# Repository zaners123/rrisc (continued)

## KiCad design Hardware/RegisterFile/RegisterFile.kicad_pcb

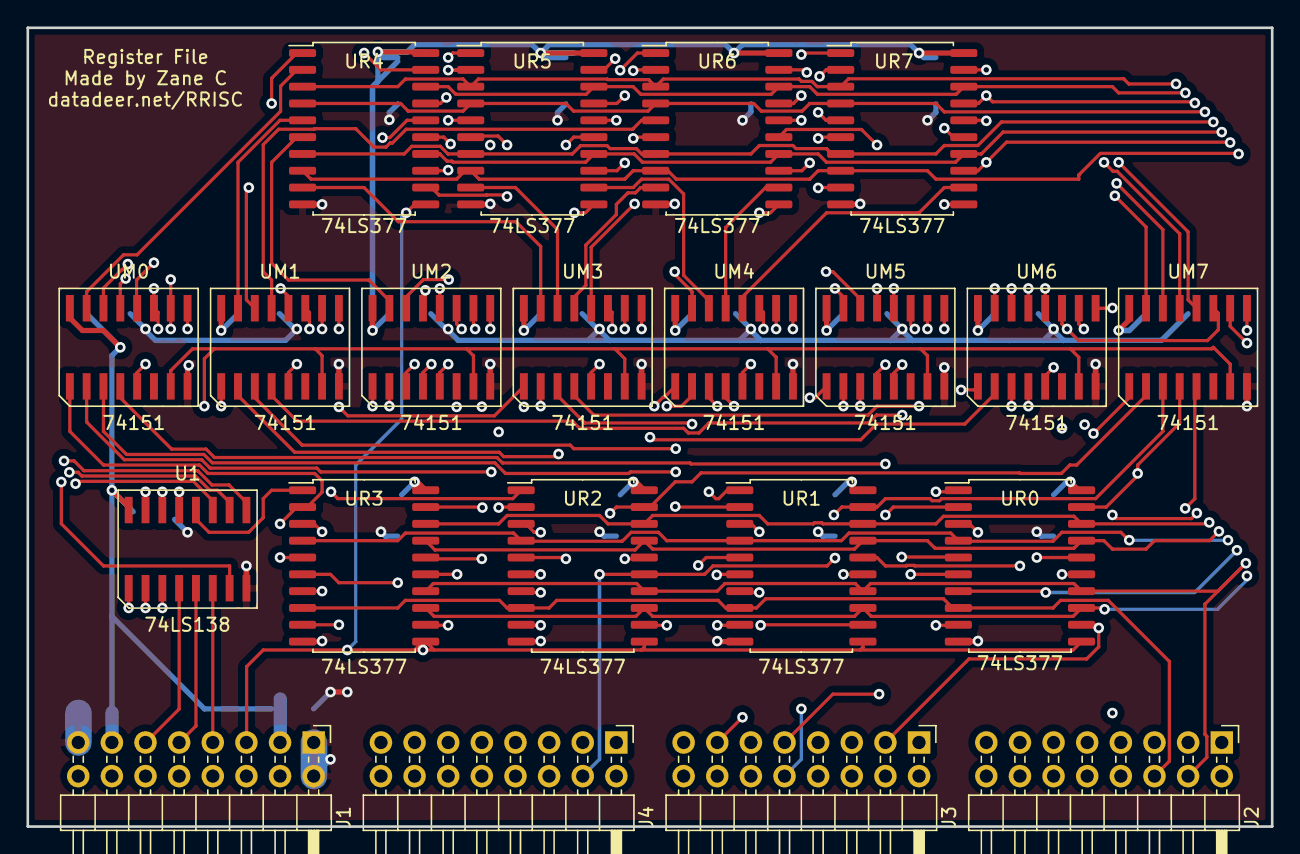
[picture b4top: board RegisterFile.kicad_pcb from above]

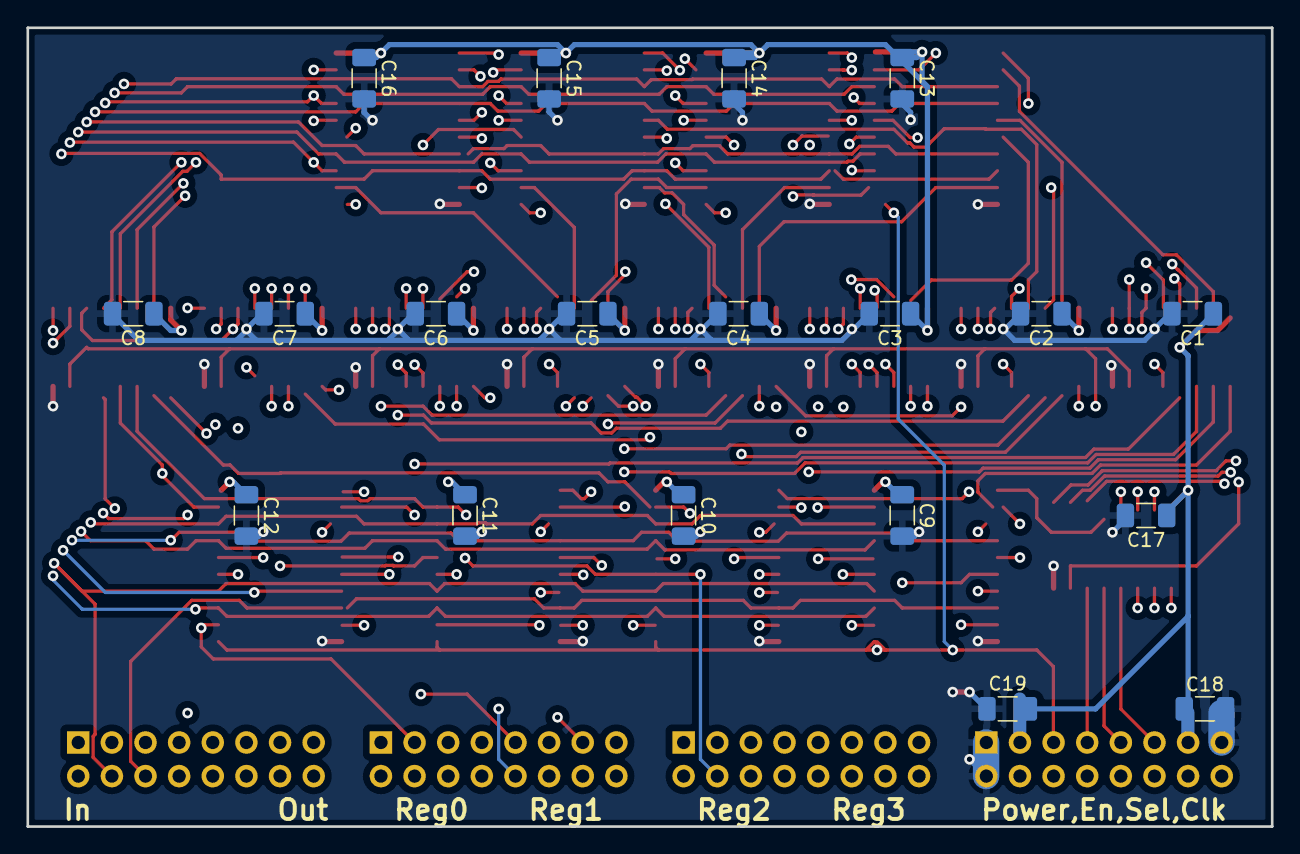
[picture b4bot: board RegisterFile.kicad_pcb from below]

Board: 4 copper layers, 94.0 x 60.3 mm, 40 parts (19 on the bottom side), 101 nets.

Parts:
C1, C2, C3, C4, C5, C6, C7, C8, C9, C10, C11, C12, C13, C14, C15, C16, C17, C18, C19: .1uF; C_1206_3216Metric_Pad1.33x1.80mm_HandSolder
J1, J2, J3, J4: Conn_02x08_Odd_Even; PinHeader_2x08_P2.54mm_Horizontal
U1: 74LS138; R-PDSO-G16
UM0, UM1, UM2, UM3, UM4, UM5, UM6, UM7: 74151; R-PDSO-G16
UR0, UR1, UR2, UR3, UR4, UR5, UR6, UR7: 74LS377; SOIC-20W_7.5x12.8mm_P1.27mm

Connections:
/CLK: J1.5, UR0.11 (CP), UR1.11 (CP), UR2.11 (CP), UR3.11 (CP), UR4.11 (CP), UR5.11 (CP), UR6.11 (CP), UR7.11 (CP)
/DATAIN0: J2.7, UR0.3 (D0), UR1.3 (D0), UR2.3 (D0), UR3.3 (D0), UR4.3 (D0), UR5.3 (D0), UR6.3 (D0), UR7.3 (D0)
/DATAIN1: J2.8, UR0.4 (D1), UR1.4 (D1), UR2.4 (D1), UR3.4 (D1), UR4.4 (D1), UR5.4 (D1), UR6.4 (D1), UR7.4 (D1)
/DATAIN2: J2.5, UR0.7 (D2), UR1.7 (D2), UR2.7 (D2), UR3.7 (D2), UR4.7 (D2), UR5.7 (D2), UR6.7 (D2), UR7.7 (D2)
/DATAIN3: J2.6, UR0.8 (D3), UR1.8 (D3), UR2.8 (D3), UR3.8 (D3), UR4.8 (D3), UR5.8 (D3), UR6.8 (D3), UR7.8 (D3)
/DATAIN4: J2.3, UR0.13 (D4), UR1.13 (D4), UR2.13 (D4), UR3.13 (D4), UR4.13 (D4), UR5.13 (D4), UR6.13 (D4), UR7.13 (D4)
/DATAIN5: J2.4, UR0.14 (D5), UR1.14 (D5), UR2.14 (D5), UR3.14 (D5), UR4.14 (D5), UR5.14 (D5), UR6.14 (D5), UR7.14 (D5)
/DATAIN6: J2.1, UR0.17 (D6), UR1.17 (D6), UR2.17 (D6), UR3.17 (D6), UR4.17 (D6), UR5.17 (D6), UR6.17 (D6), UR7.17 (D6)
/DATAIN7: J2.2, UR0.18 (D7), UR1.18 (D7), UR2.18 (D7), UR3.18 (D7), UR4.18 (D7), UR5.18 (D7), UR6.18 (D7), UR7.18 (D7)
/DATAOUT0: J2.15, UM0.5 (Q)
/DATAOUT1: J2.16, UM1.5 (Q)
/DATAOUT2: J2.13, UM2.5 (Q)
/DATAOUT3: J2.14, UM3.5 (Q)
/DATAOUT4: J2.11, UM4.5 (Q)
/DATAOUT5: J2.12, UM5.5 (Q)
/DATAOUT6: J2.9, UM6.5 (Q)
/DATAOUT7: J2.10, UM7.5 (Q)
/READID0: J1.16, UM0.11 (S0), UM1.11 (S0), UM2.11 (S0), UM3.11 (S0), UM4.11 (S0), UM5.11 (S0), UM6.11 (S0), UM7.11 (S0)
/READID1: J1.14, UM0.10 (S1), UM1.10 (S1), UM2.10 (S1), UM3.10 (S1), UM4.10 (S1), UM5.10 (S1), UM6.10 (S1), UM7.10 (S1)
/READID2: J1.12, UM0.9 (S2), UM1.9 (S2), UM2.9 (S2), UM3.9 (S2), UM4.9 (S2), UM5.9 (S2), UM6.9 (S2), UM7.9 (S2)
/REG0_0: J3.7, UM0.4 (I0), UR0.2 (Q0)
/REG0_1: J3.8, UM1.4 (I0), UR0.5 (Q1)
/REG0_2: J3.5, UM2.4 (I0), UR0.6 (Q2)
/REG0_3: J3.6, UM3.4 (I0), UR0.9 (Q3)
/REG0_4: J3.3, UM4.4 (I0), UR0.12 (Q4)
/REG0_5: J3.4, UM5.4 (I0), UR0.15 (Q5)
/REG0_6: J3.1, UM6.4 (I0), UR0.16 (Q6)
/REG0_7: J3.2, UM7.4 (I0), UR0.19 (Q7)
/REG1_0: J3.15, UM0.3 (I1), UR1.2 (Q0)
/REG1_1: J3.16, UM1.3 (I1), UR1.5 (Q1)
/REG1_2: J3.13, UM2.3 (I1), UR1.6 (Q2)
/REG1_3: J3.14, UM3.3 (I1), UR1.9 (Q3)
/REG1_4: J3.11, UM4.3 (I1), UR1.12 (Q4)
/REG1_5: J3.12, UM5.3 (I1), UR1.15 (Q5)
/REG1_6: J3.9, UM6.3 (I1), UR1.16 (Q6)
/REG1_7: J3.10, UM7.3 (I1), UR1.19 (Q7)
/REG2_0: J4.7, UM0.2 (I2), UR2.2 (Q0)
/REG2_1: J4.8, UM1.2 (I2), UR2.5 (Q1)
/REG2_2: J4.5, UM2.2 (I2), UR2.6 (Q2)
/REG2_3: J4.6, UM3.2 (I2), UR2.9 (Q3)
/REG2_4: J4.3, UM4.2 (I2), UR2.12 (Q4)
/REG2_5: J4.4, UM5.2 (I2), UR2.15 (Q5)
/REG2_6: J4.1, UM6.2 (I2), UR2.16 (Q6)
/REG2_7: J4.2, UM7.2 (I2), UR2.19 (Q7)
/REG3_0: J4.15, UM0.1 (I3), UR3.2 (Q0)
/REG3_1: J4.16, UM1.1 (I3), UR3.5 (Q1)
/REG3_2: J4.13, UM2.1 (I3), UR3.6 (Q2)
/REG3_3: J4.14, UM3.1 (I3), UR3.9 (Q3)
/REG3_4: J4.11, UM4.1 (I3), UR3.12 (Q4)
/REG3_5: J4.12, UM5.1 (I3), UR3.15 (Q5)
/REG3_6: J4.9, UM6.1 (I3), UR3.16 (Q6)
/REG3_7: J4.10, UM7.1 (I3), UR3.19 (Q7)
/REG4_0: UM0.15 (I4), UR4.2 (Q0)
/REG4_1: UM1.15 (I4), UR4.5 (Q1)
/REG4_2: UM2.15 (I4), UR4.6 (Q2)
/REG4_3: UM3.15 (I4), UR4.9 (Q3)
/REG4_4: UM4.15 (I4), UR4.12 (Q4)
/REG4_5: UM5.15 (I4), UR4.15 (Q5)
/REG4_6: UM6.15 (I4), UR4.16 (Q6)
/REG4_7: UM7.15 (I4), UR4.19 (Q7)
/REG5_0: UM0.14 (I5), UR5.2 (Q0)
/REG5_1: UM1.14 (I5), UR5.5 (Q1)
/REG5_2: UM2.14 (I5), UR5.6 (Q2)
/REG5_3: UM3.14 (I5), UR5.9 (Q3)
/REG5_4: UM4.14 (I5), UR5.12 (Q4)
/REG5_5: UM5.14 (I5), UR5.15 (Q5)
/REG5_6: UM6.14 (I5), UR5.16 (Q6)
/REG5_7: UM7.14 (I5), UR5.19 (Q7)
/REG6_0: UM0.13 (I6), UR6.2 (Q0)
/REG6_1: UM1.13 (I6), UR6.5 (Q1)
/REG6_2: UM2.13 (I6), UR6.6 (Q2)
/REG6_3: UM3.13 (I6), UR6.9 (Q3)
/REG6_4: UM4.13 (I6), UR6.12 (Q4)
/REG6_5: UM5.13 (I6), UR6.15 (Q5)
/REG6_6: UM6.13 (I6), UR6.16 (Q6)
/REG6_7: UM7.13 (I6), UR6.19 (Q7)
/REG7_0: UM0.12 (I7), UR7.2 (Q0)
/REG7_1: UM1.12 (I7), UR7.5 (Q1)
/REG7_2: UM2.12 (I7), UR7.6 (Q2)
/REG7_3: UM3.12 (I7), UR7.9 (Q3)
/REG7_4: UM4.12 (I7), UR7.12 (Q4)
/REG7_5: UM5.12 (I7), UR7.15 (Q5)
/REG7_6: UM6.12 (I7), UR7.16 (Q6)
/REG7_7: UM7.12 (I7), UR7.19 (Q7)
/Regs/~WRITESEL0: U1.15 (~Y0), UR0.1 (~E)
/Regs/~WRITESEL1: U1.14 (~Y1), UR1.1 (~E)
/Regs/~WRITESEL2: U1.13 (~Y2), UR2.1 (~E)
/Regs/~WRITESEL3: U1.12 (~Y3), UR3.1 (~E)
/Regs/~WRITESEL4: U1.11 (~Y4), UR4.1 (~E)
/Regs/~WRITESEL5: U1.10 (~Y5), UR5.1 (~E)
/Regs/~WRITESEL6: U1.9 (~Y6), UR6.1 (~E)
/Regs/~WRITESEL7: U1.7 (~Y7), UR7.1 (~E)
/WEN2: J1.7, U1.6 (G1)
/WRITEID0: J1.10, U1.1 (A0)
/WRITEID1: J1.8, U1.2 (A1)
/WRITEID2: J1.6, U1.3 (A2)
/~REN: J1.4, UM0.7 (~E), UM1.7 (~E), UM2.7 (~E), UM3.7 (~E), UM4.7 (~E), UM5.7 (~E), UM6.7 (~E), UM7.7 (~E)
/~WEN0: J1.11, U1.4 (~G2A)
/~WEN1: J1.9, U1.5 (~G2B)
GND: C1.2, C2.2, C3.2, C4.2, C5.2, C6.2, C7.2, C8.2, C9.2, C10.2, C11.2, C12.2, C13.2, C14.2, C15.2, C16.2, C17.2, C18.2, C19.2, J1.1, J1.2, J1.15, U1.8 (GND), UM0.8 (GND), UM1.8 (GND), UM2.8 (GND), UM3.8 (GND), UM4.8 (GND), UM5.8 (GND), UM6.8 (GND), UM7.8 (GND), UR0.10 (GND), UR1.10 (GND), UR2.10 (GND), UR3.10 (GND), UR4.10 (GND), UR5.10 (GND), UR6.10 (GND), UR7.10 (GND)
VCC: C1.1, C2.1, C3.1, C4.1, C5.1, C6.1, C7.1, C8.1, C9.1, C10.1, C11.1, C12.1, C13.1, C14.1, C15.1, C16.1, C17.1, C18.1, C19.1, J1.3, J1.13, U1.16 (VCC), UM0.16 (VCC), UM1.16 (VCC), UM2.16 (VCC), UM3.16 (VCC), UM4.16 (VCC), UM5.16 (VCC), UM6.16 (VCC), UM7.16 (VCC), UR0.20 (VCC), UR1.20 (VCC), UR2.20 (VCC), UR3.20 (VCC), UR4.20 (VCC), UR5.20 (VCC), UR6.20 (VCC), UR7.20 (VCC)

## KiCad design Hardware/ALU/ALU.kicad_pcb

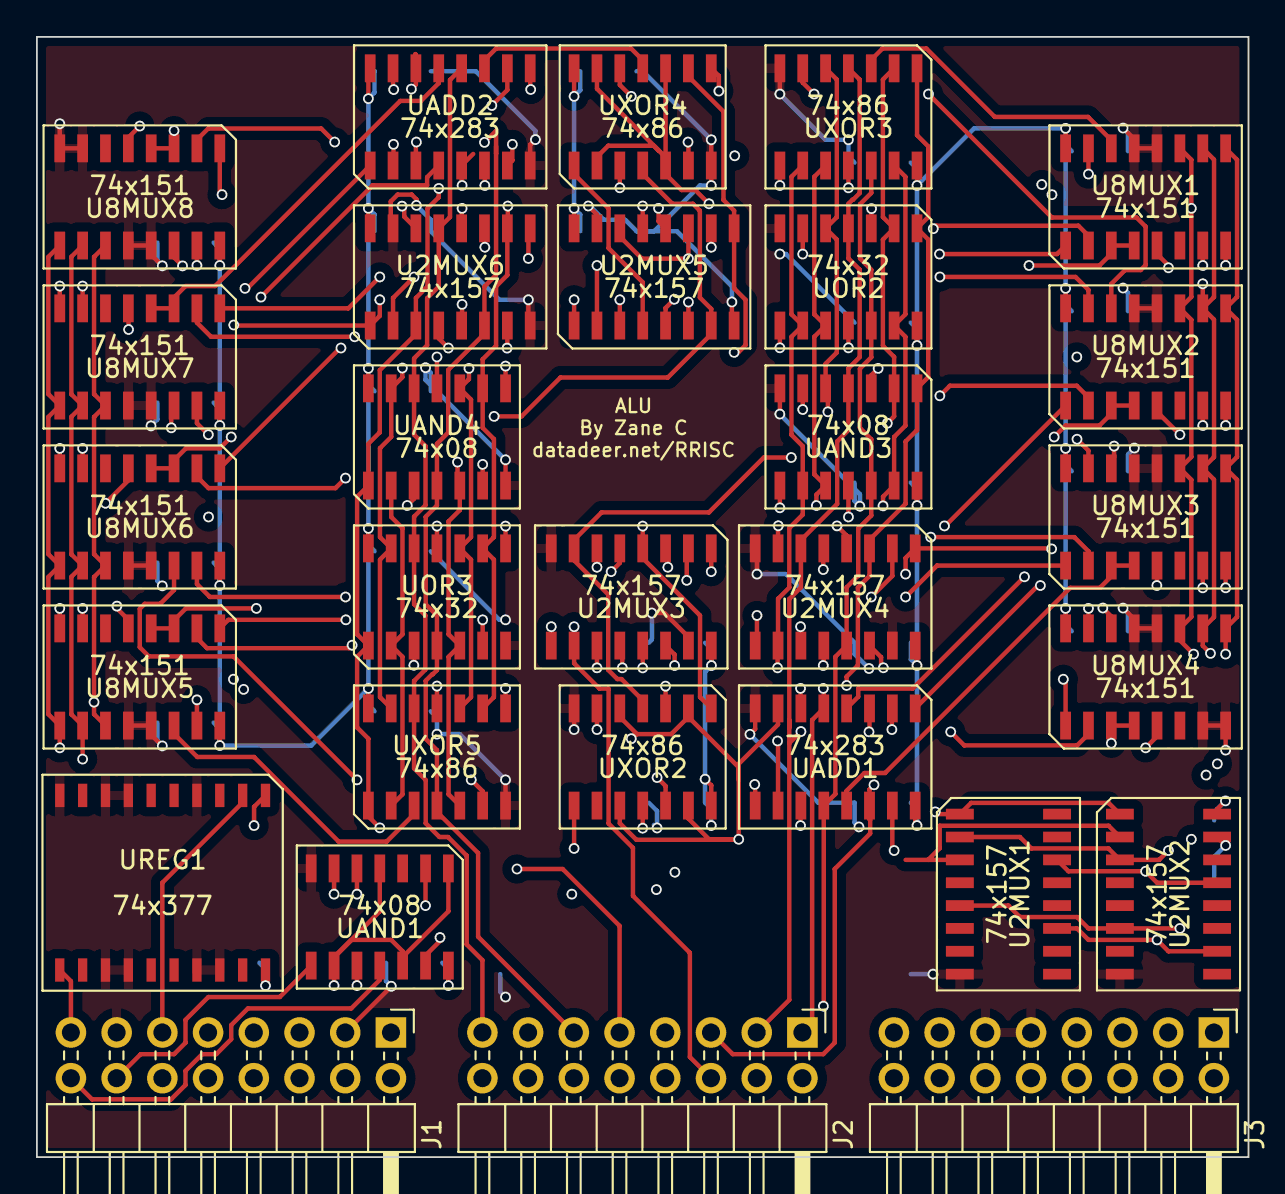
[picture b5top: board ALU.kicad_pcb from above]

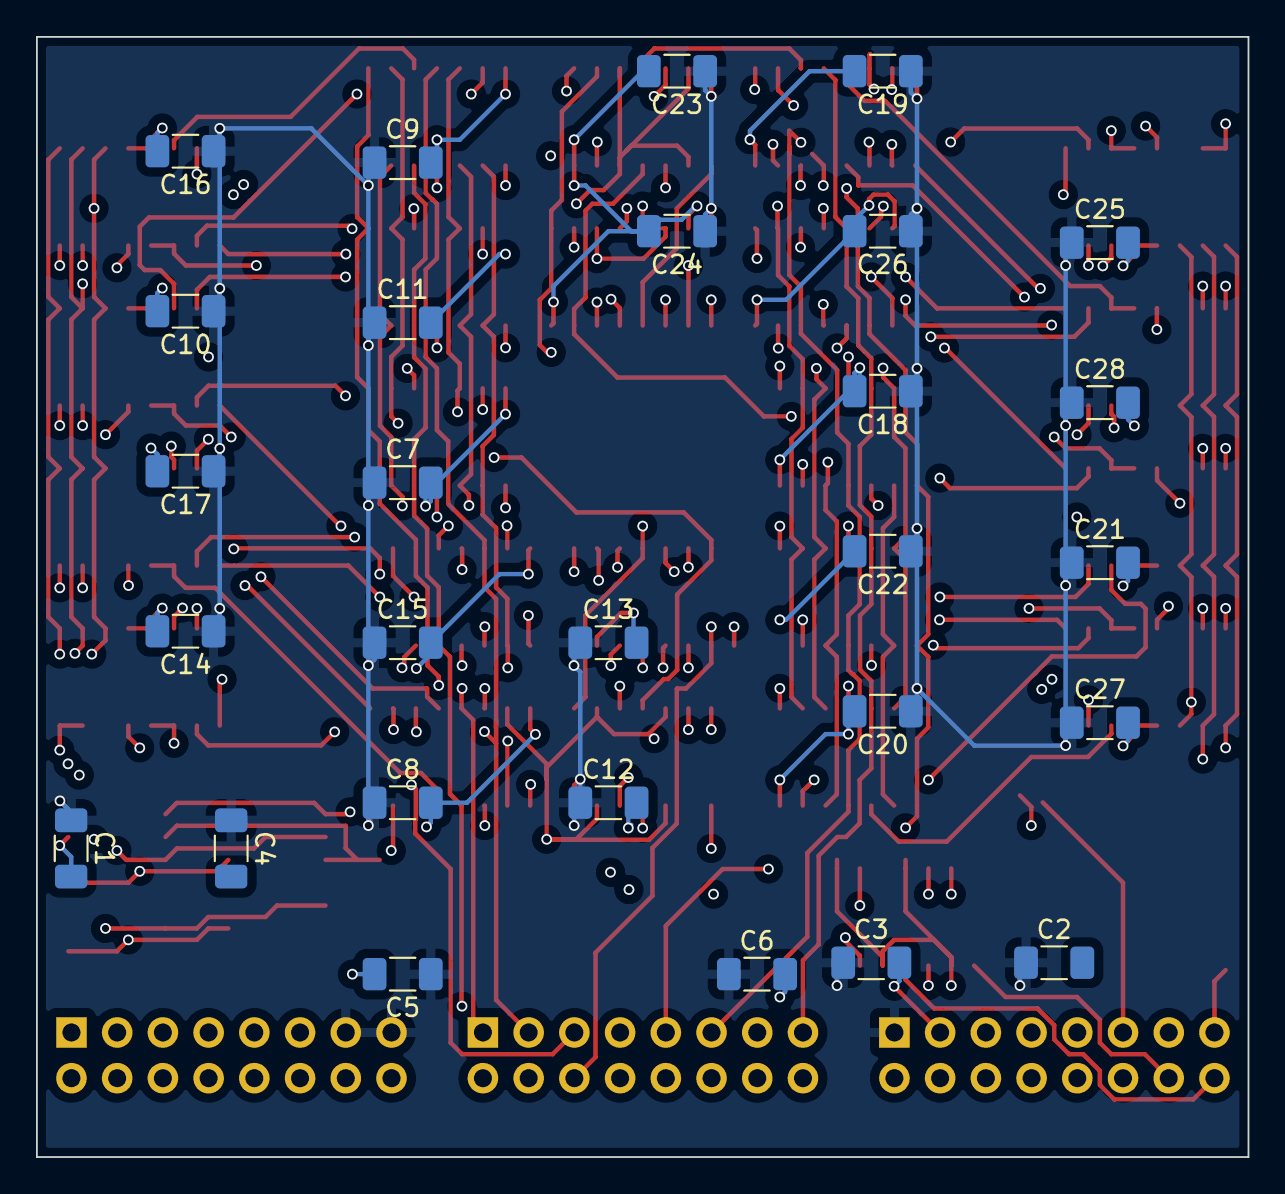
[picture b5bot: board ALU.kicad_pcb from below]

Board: 4 copper layers, 67.3 x 62.2 mm, 57 parts (28 on the bottom side), 109 nets.

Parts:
C1, C2, C3, C4, C5, C6, C7, C8, C9, C10, C11, C12, C13, C14, C15, C16, C17, C18, C19, C20, C21, C22, C23, C24, C25, C26, C27, C28: .1uF; C_1206_3216Metric_Pad1.33x1.80mm_HandSolder
J1, J2, J3: connector_2x8; PinHeader_2x08_P2.54mm_Horizontal
U2MUX1, U2MUX2, U2MUX3, U2MUX4, U2MUX5, U2MUX6: 74x157; D_R-PDSO-G16
U8MUX1, U8MUX2, U8MUX3, U8MUX4, U8MUX5, U8MUX6, U8MUX7, U8MUX8: 74x151; D_R-PDSO-G16
UADD1, UADD2: 74x283; D_R-PDSO-G16
UAND1, UAND3, UAND4: 74x08; D_R-PDSO-G14
UOR2, UOR3: 74x32; D_R-PDSO-G14
UREG1: 74x377; ON-SOIC20-WB
UXOR2, UXOR3, UXOR4, UXOR5: 74x86; D_R-PDSO-G14

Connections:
/CARRY_BETWEEN: UADD1.9 (C4), UADD2.7 (C0)
/CHANGEOUT: J1.5, UAND1.1, UAND1.4, UAND1.9, UAND1.12
/CLK: J1.15, UREG1.11 (CP)
/IN_ACC0: J2.1, U2MUX4.3 (I1a), UADD1.5 (A1), UAND3.1, UOR2.1, UXOR3.1
/IN_ACC1: J2.3, U2MUX4.6 (I1b), UADD1.3 (A2), UAND3.4, UOR2.4, UXOR3.4
/IN_ACC2: J2.5, U2MUX4.10 (I1c), UADD1.14 (A3), UAND3.9, UOR2.9, UXOR3.9
/IN_ACC3: J2.7, U2MUX4.13 (I1d), UADD1.12 (A4), UAND3.12, UOR2.12, UXOR3.12
/IN_ACC4: J2.9, U2MUX6.3 (I1a), UADD2.5 (A1), UAND4.1, UOR3.1, UXOR5.1
/IN_ACC5: J2.11, U2MUX6.6 (I1b), UADD2.3 (A2), UAND4.4, UOR3.4, UXOR5.4
/IN_ACC6: J2.13, U2MUX6.10 (I1c), UADD2.14 (A3), UAND4.9, UOR3.9, UXOR5.9
/IN_ACC7: J2.15, U2MUX6.13 (I1d), UADD2.12 (A4), UAND4.12, UOR3.12, UXOR5.12
/IN_IMMEDIATE0: J1.2, U2MUX3.2 (I0a), UAND1.2
/IN_IMMEDIATE1: J1.4, U2MUX3.5 (I0b), UAND1.5
/IN_IMMEDIATE2: J1.6, U2MUX3.11 (I0c), UAND1.10
/IN_IMMEDIATE3: J1.8, U2MUX3.14 (I0d), UAND1.13
/IN_OPCODE0: J3.7, U2MUX3.1 (S), U2MUX4.1 (S), U2MUX5.1 (S), U2MUX6.1 (S)
/IN_OPCODE1: J3.5, U8MUX1.11 (S0), U8MUX2.11 (S0), U8MUX3.11 (S0), U8MUX4.11 (S0), U8MUX5.11 (S0), U8MUX6.11 (S0), U8MUX7.11 (S0), U8MUX8.11 (S0), UADD1.7 (C0), UXOR2.2, UXOR2.5, UXOR2.10, UXOR2.13, UXOR4.2, UXOR4.5, UXOR4.10, UXOR4.13
/IN_OPCODE2: J3.3, U2MUX5.2 (I0a), U2MUX5.5 (I0b), U2MUX5.11 (I0c), U2MUX5.14 (I0d), U8MUX1.10 (S1), U8MUX2.10 (S1), U8MUX3.10 (S1), U8MUX4.10 (S1), U8MUX5.10 (S1), U8MUX6.10 (S1), U8MUX7.10 (S1), U8MUX8.10 (S1)
/IN_OPCODE3: J3.1, U8MUX1.9 (S2), U8MUX2.9 (S2), U8MUX3.9 (S2), U8MUX4.9 (S2), U8MUX5.9 (S2), U8MUX6.9 (S2), U8MUX7.9 (S2), U8MUX8.9 (S2)
/IN_REGDATA0: J2.2, U2MUX3.3 (I1a), U2MUX4.2 (I0a)
/IN_REGDATA1: J2.4, U2MUX3.6 (I1b), U2MUX4.5 (I0b)
/IN_REGDATA2: J2.6, U2MUX3.10 (I1c), U2MUX4.11 (I0c)
/IN_REGDATA3: J2.8, U2MUX3.13 (I1d), U2MUX4.14 (I0d)
/IN_REGDATA4: J2.10, U2MUX5.3 (I1a), U2MUX6.2 (I0a)
/IN_REGDATA5: J2.12, U2MUX5.6 (I1b), U2MUX6.5 (I0b)
/IN_REGDATA6: J2.14, U2MUX5.10 (I1c), U2MUX6.11 (I0c)
/IN_REGDATA7: J2.16, U2MUX5.13 (I1d), U2MUX6.14 (I0d)
/OUT_CARRY: J1.11, UREG1.2 (Q0)
/OUT_RESULT0: J3.16, U2MUX1.4 (Za)
/OUT_RESULT1: J3.14, U2MUX1.7 (Zb)
/OUT_RESULT2: J3.12, U2MUX1.9 (Zc)
/OUT_RESULT3: J3.10, U2MUX1.12 (Zd)
/OUT_RESULT4: J3.8, U2MUX2.4 (Za)
/OUT_RESULT5: J3.6, U2MUX2.7 (Zb)
/OUT_RESULT6: J3.4, U2MUX2.9 (Zc)
/OUT_RESULT7: J3.2, U2MUX2.12 (Zd)
/OUT_RX_ID0: J1.10, UAND1.3
/OUT_RX_ID1: J1.12, UAND1.6
/OUT_RX_ID2: J1.14, UAND1.8
/OUT_RX_ID3: J1.16, UAND1.11
/PRESWAPPED0: U2MUX1.2 (I0a), U2MUX2.3 (I1a), U8MUX1.5 (Q)
/PRESWAPPED1: U2MUX1.5 (I0b), U2MUX2.6 (I1b), U8MUX2.5 (Q)
/PRESWAPPED2: U2MUX1.11 (I0c), U2MUX2.10 (I1c), U8MUX3.5 (Q)
/PRESWAPPED3: U2MUX1.14 (I0d), U2MUX2.13 (I1d), U8MUX4.5 (Q)
/PRESWAPPED4: U2MUX1.3 (I1a), U2MUX2.2 (I0a), U8MUX5.5 (Q)
/PRESWAPPED5: U2MUX1.6 (I1b), U2MUX2.5 (I0b), U8MUX6.5 (Q)
/PRESWAPPED6: U2MUX1.10 (I1c), U2MUX2.11 (I0c), U8MUX7.5 (Q)
/PRESWAPPED7: U2MUX1.13 (I1d), U2MUX2.14 (I0d), U8MUX8.5 (Q)
/SWAP_NIBBLES: J1.9, U2MUX1.1 (S), U2MUX2.1 (S)
/lower/OP0_BIT0: U8MUX1.3 (I1), U8MUX1.4 (I0), UADD1.4 (S1)
/lower/OP0_BIT1: U8MUX2.3 (I1), U8MUX2.4 (I0), UADD1.1 (S2)
/lower/OP0_BIT2: U8MUX3.3 (I1), U8MUX3.4 (I0), UADD1.13 (S3)
/lower/OP0_BIT3: U8MUX4.3 (I1), U8MUX4.4 (I0), UADD1.10 (S4)
/lower/OP2_BIT0: U8MUX1.2 (I2), UAND3.3
/lower/OP2_BIT1: U8MUX2.2 (I2), UAND3.6
/lower/OP2_BIT2: U8MUX3.2 (I2), UAND3.8
/lower/OP2_BIT3: U8MUX4.2 (I2), UAND3.11
/lower/OP3_BIT0: U2MUX4.4 (Za), U8MUX1.1 (I3)
/lower/OP3_BIT1: U2MUX4.7 (Zb), U8MUX2.1 (I3)
/lower/OP3_BIT2: U2MUX4.9 (Zc), U8MUX3.1 (I3)
/lower/OP3_BIT3: U2MUX4.12 (Zd), U8MUX4.1 (I3)
/lower/OP4_BIT0: U8MUX1.15 (I4), UOR2.3
/lower/OP4_BIT1: U8MUX2.15 (I4), UOR2.6
/lower/OP4_BIT2: U8MUX3.15 (I4), UOR2.8
/lower/OP4_BIT3: U8MUX4.15 (I4), UOR2.11
/lower/OP5_BIT0: U8MUX1.14 (I5), UXOR3.3
/lower/OP5_BIT1: U8MUX2.14 (I5), UXOR3.6
/lower/OP5_BIT2: U8MUX3.14 (I5), UXOR3.8
/lower/OP5_BIT3: U8MUX4.14 (I5), UXOR3.11
/lower/OPERANDB0: U2MUX3.4 (Za), UAND3.2, UOR2.2, UXOR2.1, UXOR3.2
/lower/OPERANDB1: U2MUX3.7 (Zb), UAND3.5, UOR2.5, UXOR2.4, UXOR3.5
/lower/OPERANDB2: U2MUX3.9 (Zc), UAND3.10, UOR2.10, UXOR2.9, UXOR3.10
/lower/OPERANDB3: U2MUX3.12 (Zd), UAND3.13, UOR2.13, UXOR2.12, UXOR3.13
/upper/CARRY_OUT: UADD2.9 (C4), UREG1.3 (D0)
/upper/OP0_BIT0: U8MUX5.3 (I1), U8MUX5.4 (I0), UADD2.4 (S1)
/upper/OP0_BIT1: U8MUX6.3 (I1), U8MUX6.4 (I0), UADD2.1 (S2)
/upper/OP0_BIT2: U8MUX7.3 (I1), U8MUX7.4 (I0), UADD2.13 (S3)
/upper/OP0_BIT3: U8MUX8.3 (I1), U8MUX8.4 (I0), UADD2.10 (S4)
/upper/OP2_BIT0: U8MUX5.2 (I2), UAND4.3
/upper/OP2_BIT1: U8MUX6.2 (I2), UAND4.6
/upper/OP2_BIT2: U8MUX7.2 (I2), UAND4.8
/upper/OP2_BIT3: U8MUX8.2 (I2), UAND4.11
/upper/OP3_BIT0: U2MUX6.4 (Za), U8MUX5.1 (I3)
/upper/OP3_BIT1: U2MUX6.7 (Zb), U8MUX6.1 (I3)
/upper/OP3_BIT2: U2MUX6.9 (Zc), U8MUX7.1 (I3)
/upper/OP3_BIT3: U2MUX6.12 (Zd), U8MUX8.1 (I3)
/upper/OP4_BIT0: U8MUX5.15 (I4), UOR3.3
/upper/OP4_BIT1: U8MUX6.15 (I4), UOR3.6
/upper/OP4_BIT2: U8MUX7.15 (I4), UOR3.8
/upper/OP4_BIT3: U8MUX8.15 (I4), UOR3.11
/upper/OP5_BIT0: U8MUX5.14 (I5), UXOR5.3
/upper/OP5_BIT1: U8MUX6.14 (I5), UXOR5.6
/upper/OP5_BIT2: U8MUX7.14 (I5), UXOR5.8
/upper/OP5_BIT3: U8MUX8.14 (I5), UXOR5.11
/upper/OPERANDB0: U2MUX5.4 (Za), UAND4.2, UOR3.2, UXOR4.1, UXOR5.2
/upper/OPERANDB1: U2MUX5.7 (Zb), UAND4.5, UOR3.5, UXOR4.4, UXOR5.5
/upper/OPERANDB2: U2MUX5.9 (Zc), UAND4.10, UOR3.10, UXOR4.9, UXOR5.10
/upper/OPERANDB3: U2MUX5.12 (Zd), UAND4.13, UOR3.13, UXOR4.12, UXOR5.13
/~CARRY_WE: J1.7, UREG1.1 (~E)
GND: C1.2, C2.2, C3.2, C4.2, C5.2, C6.2, C7.2, C8.2, C9.2, C10.2, C11.2, C12.2, C13.2, C14.2, C15.2, C16.2, C17.2, C18.2, C19.2, C20.2, C21.2, C22.2, C23.2, C24.2, C25.2, C26.2, C27.2, C28.2, J1.3, J1.13, J3.9, J3.11, U2MUX1.8 (GND), U2MUX1.15 (E), U2MUX2.8 (GND), U2MUX2.15 (E), U2MUX3.8 (GND), U2MUX3.15 (E), U2MUX4.8 (GND), U2MUX4.15 (E), U2MUX5.8 (GND), U2MUX5.15 (E), U2MUX6.8 (GND), U2MUX6.15 (E), U8MUX1.7 (~E), U8MUX1.8 (GND), U8MUX1.12 (I7), U8MUX1.13 (I6), U8MUX2.7 (~E), U8MUX2.8 (GND), U8MUX2.12 (I7), U8MUX2.13 (I6), U8MUX3.7 (~E), U8MUX3.8 (GND), U8MUX3.12 (I7), U8MUX3.13 (I6), U8MUX4.7 (~E), U8MUX4.8 (GND), U8MUX4.12 (I7), U8MUX4.13 (I6), U8MUX5.7 (~E), U8MUX5.8 (GND), U8MUX5.12 (I7), U8MUX5.13 (I6), U8MUX6.7 (~E), U8MUX6.8 (GND), U8MUX6.12 (I7), U8MUX6.13 (I6), U8MUX7.7 (~E), U8MUX7.8 (GND), U8MUX7.12 (I7), U8MUX7.13 (I6), U8MUX8.7 (~E), U8MUX8.8 (GND), U8MUX8.12 (I7), U8MUX8.13 (I6), UADD1.8 (GND), UADD2.8 (GND), UAND1.7 (GND), UAND3.7 (GND), UAND4.7 (GND), UOR2.7 (GND), UOR3.7 (GND), UREG1.4 (D1), UREG1.7 (D2), UREG1.8 (D3), UREG1.10 (GND), UREG1.13 (D4), UREG1.14 (D5), UREG1.17 (D6), UREG1.18 (D7), UXOR2.7 (GND), UXOR3.7 (GND), UXOR4.7 (GND), UXOR5.7 (GND)
unnamed: UADD1.2 (B2), UXOR2.6
unnamed: UADD1.6 (B1), UXOR2.3
unnamed: UADD1.11 (B4), UXOR2.11
unnamed: UADD1.15 (B3), UXOR2.8
unnamed: UADD2.2 (B2), UXOR4.6
unnamed: UADD2.6 (B1), UXOR4.3
unnamed: UADD2.11 (B4), UXOR4.11
unnamed: UADD2.15 (B3), UXOR4.8
VCC: C1.1, C2.1, C3.1, C4.1, C5.1, C6.1, C7.1, C8.1, C9.1, C10.1, C11.1, C12.1, C13.1, C14.1, C15.1, C16.1, C17.1, C18.1, C19.1, C20.1, C21.1, C22.1, C23.1, C24.1, C25.1, C26.1, C27.1, C28.1, J1.1, J3.13, J3.15, U2MUX1.16 (VCC), U2MUX2.16 (VCC), U2MUX3.16 (VCC), U2MUX4.16 (VCC), U2MUX5.16 (VCC), U2MUX6.16 (VCC), U8MUX1.16 (VCC), U8MUX2.16 (VCC), U8MUX3.16 (VCC), U8MUX4.16 (VCC), U8MUX5.16 (VCC), U8MUX6.16 (VCC), U8MUX7.16 (VCC), U8MUX8.16 (VCC), UADD1.16 (VCC), UADD2.16 (VCC), UAND1.14 (VCC), UAND3.14 (VCC), UAND4.14 (VCC), UOR2.14 (VCC), UOR3.14 (VCC), UREG1.20 (VCC), UXOR2.14 (VCC), UXOR3.14 (VCC), UXOR4.14 (VCC), UXOR5.14 (VCC)

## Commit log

2022-02-01 Progress towards having memory IO instructions.
2022-02-15 WIP - Organizing ALU, speeding up computer, and more!
    Also added a large list of conditional jumps - see ISA.md under jmp
2022-02-15 Organizing the computer some more! Now with ALU conditional jumps! (Setting the jump overrides the ALU)
2022-02-16 Fix problems
    Largest known problem/question:
    - Do I do carries in hardware or software?
2022-02-20 End of Repeat With Carry
    My last bit of documentation before asking on stackoverflow (https://stackoverflow.com/questions/71188654/would-an-instruction-set-architecture-benefit-from-both-an-adc-and-sbc-or-could/71188757#7118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
    and realizing that doing a skip-if would be much better and more versatile than a simple rwc.
2022-02-20 Improving computer - Added conditional skip instruction. This takes the place of carry, skip, rotate, and many other instructions.
    Currently working on simplifying assembler.
2022-02-22 Progress - Sometimes glitches for push/pop - Might be working apart from that
2022-03-28 About to fix computer. Haven't looked at it in a while and noticed way too many useless MUXes in the ALU
2022-04-26 Still a work in progress. Need to verify timing diagrams and get push/pop memory register to stack before considering starting hardware
2022-04-26 Fixed readme
2022-04-26 Fixing markdown
2022-04-26 Hardware completely supports subroutines and software tests were made to verify this (as shown in code.asm). This seems to work flawlessly, and after testing with more cool code (such as prime number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
2022-04-27 Starting hardware! Also currently moving ProgramCounter logic into a LogiSim module to abstract it better
2022-04-27 Started to make Schematic for the Program Counter.
    TODO: Complete schematic, buy parts, layout PCB, solder PCB.
    Then logically test the PCB using a digital oscilloscope.
    Then repeat for 4-5 other PCBs.
2022-04-29 PC PCB Progress
    Mostly done with schematic for the Program Counter. I'll order parts soon and start on the PCB design next. It'll be my first four layer board!
    Based on what I've seen so far, CMOS seems to be more prevalent than TTL, so I'll make this computer out of CMOS.
2022-05-04 PC Schematic
    Mostly finished Program Counter schematic. I'm basing the hardware largely off of TI's new HCS family of SN74HCS chips.
2022-05-09 PC Board
    Mostly done. Going to move top half down.
2022-05-10 PC Board
    Mostly done. Going to move register to the right and connect logic gates
2022-05-12 Program Counter Board
    Seems to be done. Likely be ordering very soon. Also added a debug/testpoint connector to the top so that I can probe it easier
2022-05-12 Register File Board
    Starting out the general layout
2022-05-21 Created export for Program Counter PCB V1
2022-06-25 Making Register File board in Kicad6
2022-06-25 RegisterFile Layout: Everything except the "spider" (routing the all 8 muxes each to all 8 registers might be non-trivial)
2022-06-26 RegisterFile: The layout's all done!
2022-07-08 ALU Schematic: Mostly done!
2022-07-12 ALU Schematic: A backup save before I realized Kicad doesn't seem to officially support hierarchical busses. Soon to replace all sheet busses with lines (I guess four lines isn't too many...)
2022-07-16 ALU: About to increase modularity by moving opcode parsing out of ALU onto motherboard (would turn backplane into more of a motherboard).
2022-07-16 ALU: Starting routing. Also passing this to kicad's github #collab
2022-07-17 ALU: Routing Progress
2022-07-19 Logisim: Saving before replacing ALU with mux-based-alu and before replacing von-neumann-based memory with harvard-based memory
2022-07-19 Logisim: Computer simulation with simplified memory and ALU passing all tests!
2022-07-21 Logisim: count.asm working well! Going to make MuxALU schematic now.
2022-07-28 ALUMux: Progress on routing/layout
2022-07-30 ALUMux: PCB done.
    Going to start ProgramCounter2
2022-10-24 Motherboard Significant Progress
    This involves significant buildup of the motherboard, such as the power, oscillator, and overall design.
    The motherboard schematic is in progress (some lines have yet to be connected), and the PCB layout is mostly just there to consider spacing.
2022-11-06 Switch the compiler to Java
2023-03-19 Motherboard Schematic Major Updates: - Skip implemented - Memory WB implemented Also, the JavaAssembler was somewhat updated but isn't done yet.
2023-03-29 Motherboard Layout: Most Traces Done
    ~30 traces left for motherboard, then it's all ready for ordering!
2023-03-29 Motherboard V1
2023-04-04 Motherboard V1.1
    With teardrops and other small changes
2023-04-15 Considering a ROM Programmer out of a Analog Discovery 2. Might just buy a programmer tho
2023-09-03 Java compiler paired with Arduino ROM programmer. Arduino ROM programmer fully functional.
2023-09-07 Java compiler optimized, labels working.
2023-09-14 A fully functional prime sieve to 256!
